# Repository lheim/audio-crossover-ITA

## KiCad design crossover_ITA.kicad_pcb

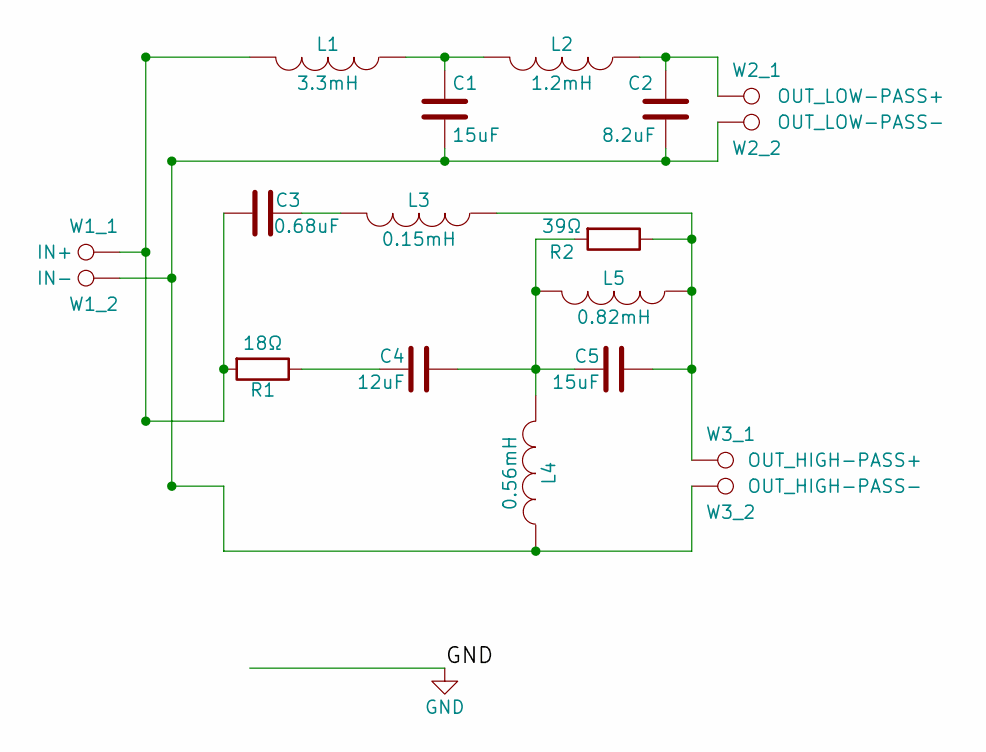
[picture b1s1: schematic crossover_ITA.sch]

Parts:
C1, C5: 15uF; C_MKTA_15_160
C2: 8.2uF; C_MKTA_8.2_250
C3: 0.68uF; C_MKTA_0.68_100
C4: 12uF; C_MKTA_12_100
L1: 3.3mH; L_HQ43_3.3_095
L2: 1.2mH; L_HQ40_1.2_112
L3: 0.15mH; L_LUT32_015_10
L4: 0.56mH; L_LU62_056_140
L5: 0.82mH; L_LU55_082_100
R1: 18Ω; R_WAX20_18_5
R2: 39Ω; R_WAX10_39_5
W1_1: IN+; 1pin
W1_2: IN-; 1pin
W2_1: OUT_LOW-PASS+; 1pin
W2_2: OUT_LOW-PASS-; 1pin
W3_1: OUT_HIGH-PASS+; 1pin
W3_2: OUT_HIGH-PASS-; 1pin

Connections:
unnamed: C1.1, L1.1, L2.2
unnamed: C1.2, C2.2, L4.1, W1_2.1, W2_2.1, W3_2.1
unnamed: C2.1, L2.1, W2_1.1
unnamed: C3.1, L1.2, R1.2, W1_1.1
unnamed: C3.2, L3.2
unnamed: C4.1, R1.1
unnamed: C4.2, C5.1, L4.2, L5.2, R2.2
unnamed: C5.2, L3.1, L5.1, R2.1, W3_1.1

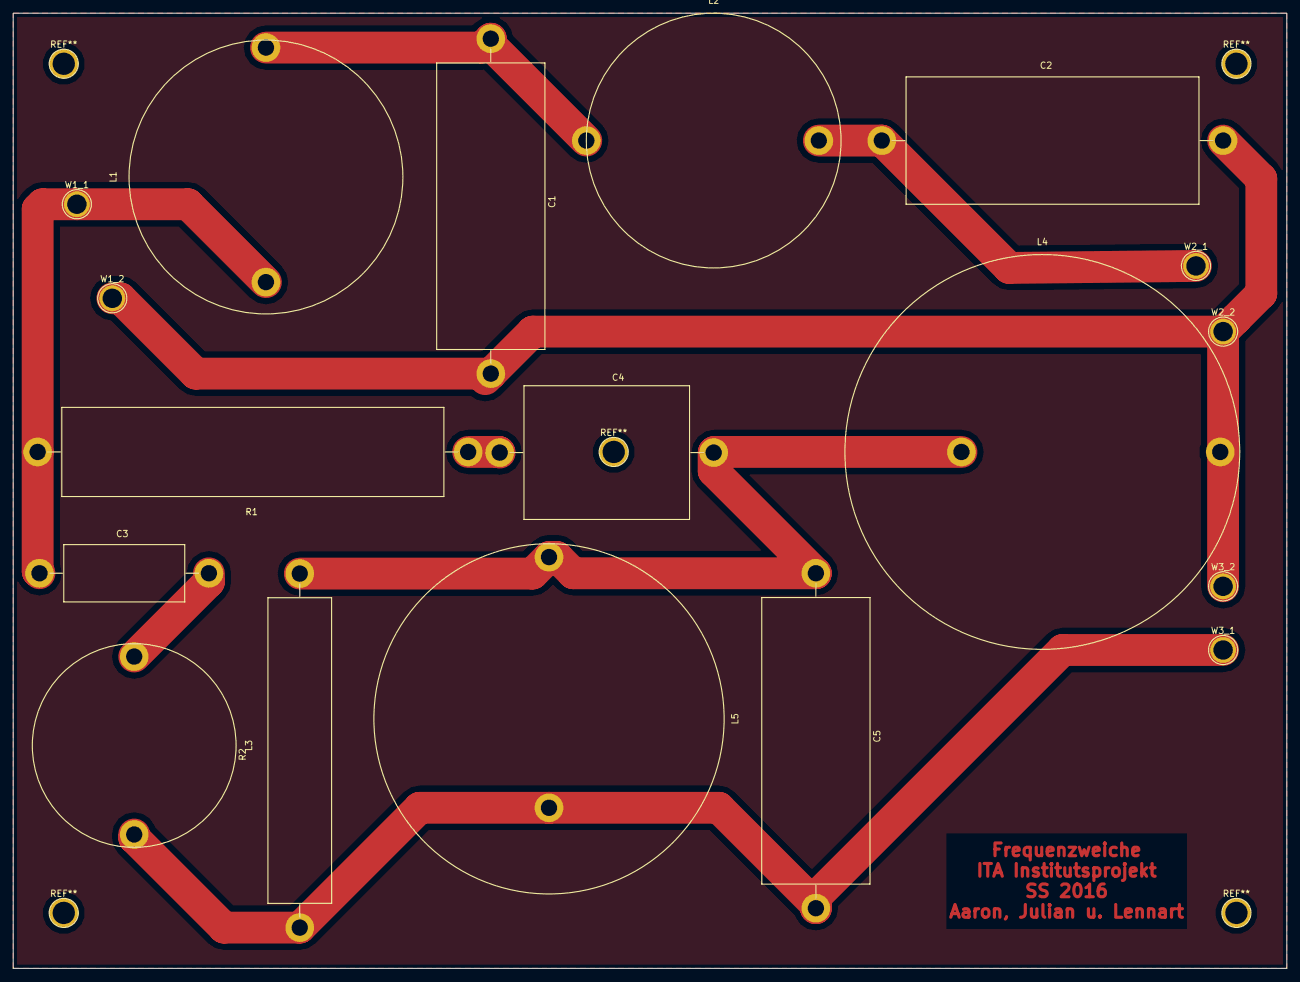
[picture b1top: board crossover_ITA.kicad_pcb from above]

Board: 2 copper layers, 200.0 x 150.0 mm, 18 parts (0 on the bottom side), 8 nets.

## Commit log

2018-07-29 init
